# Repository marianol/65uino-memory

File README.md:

# 65uino Memory Hat

This is a hack Hat for the 65uino project to extend the memory to the maximum 4Kb minus the 256 bytes of Zero Page used by the RIOT memory and registers.

Is a hack Hat because it relocates the board ROM to the hat and uses pin headers to bring the ROM pins to the hat board. You will need to add some bodge wires to extend extra pins (A12 and R/WB) not available in the ROM socket.

This board has not been tested as of Rev. 0.2

## Memory Map
RIOT $0000-$00FF
RAM  $0100-$0FFF
ROM  $1000-$1FFF

## 65uino Project
The project author is Anders Nielsen and you can findit here https://github.com/AndersBNielsen/65uino/
You'll find more details at https://hackaday.io/project/190260-65uino

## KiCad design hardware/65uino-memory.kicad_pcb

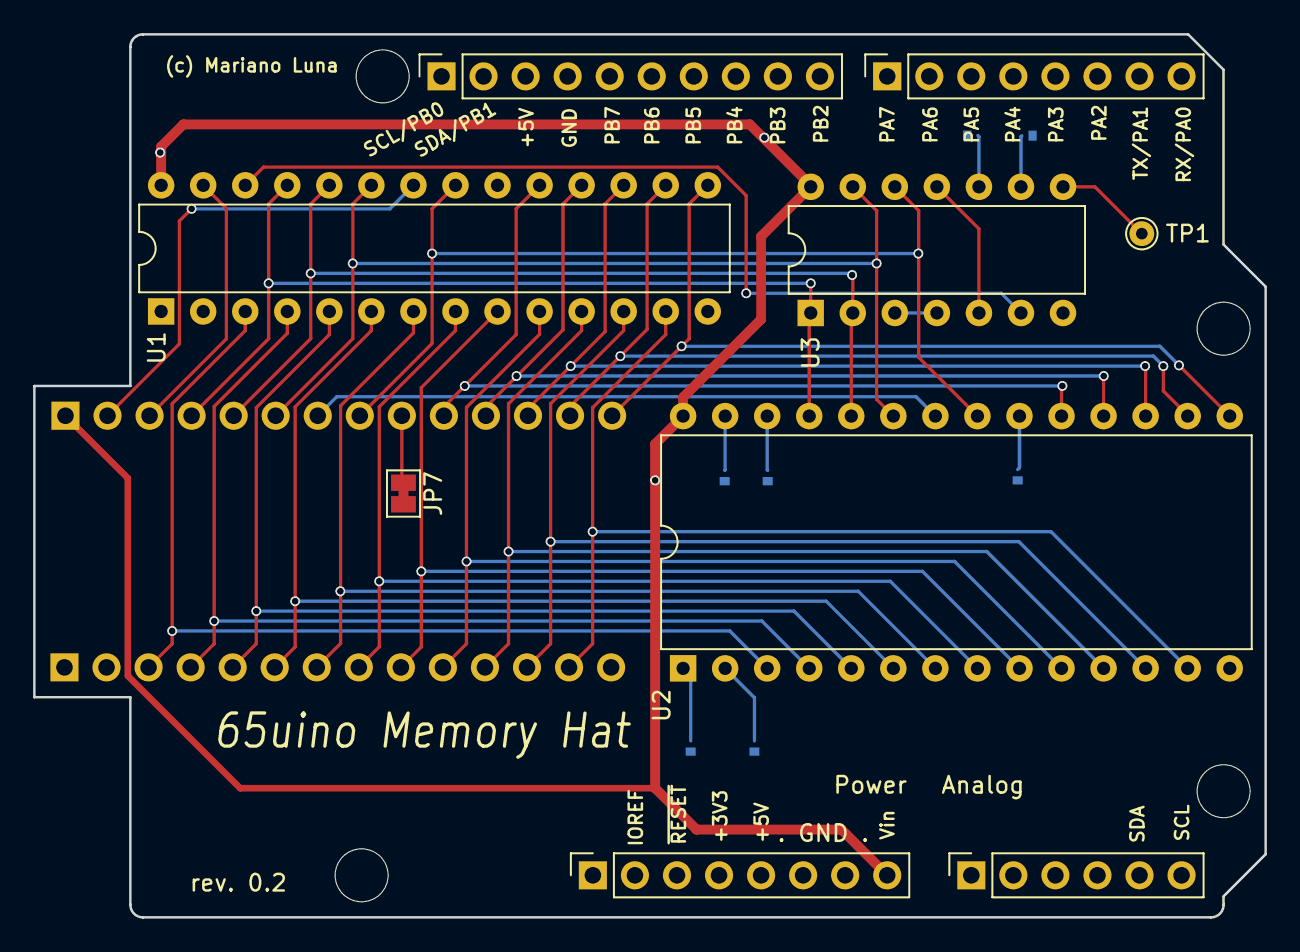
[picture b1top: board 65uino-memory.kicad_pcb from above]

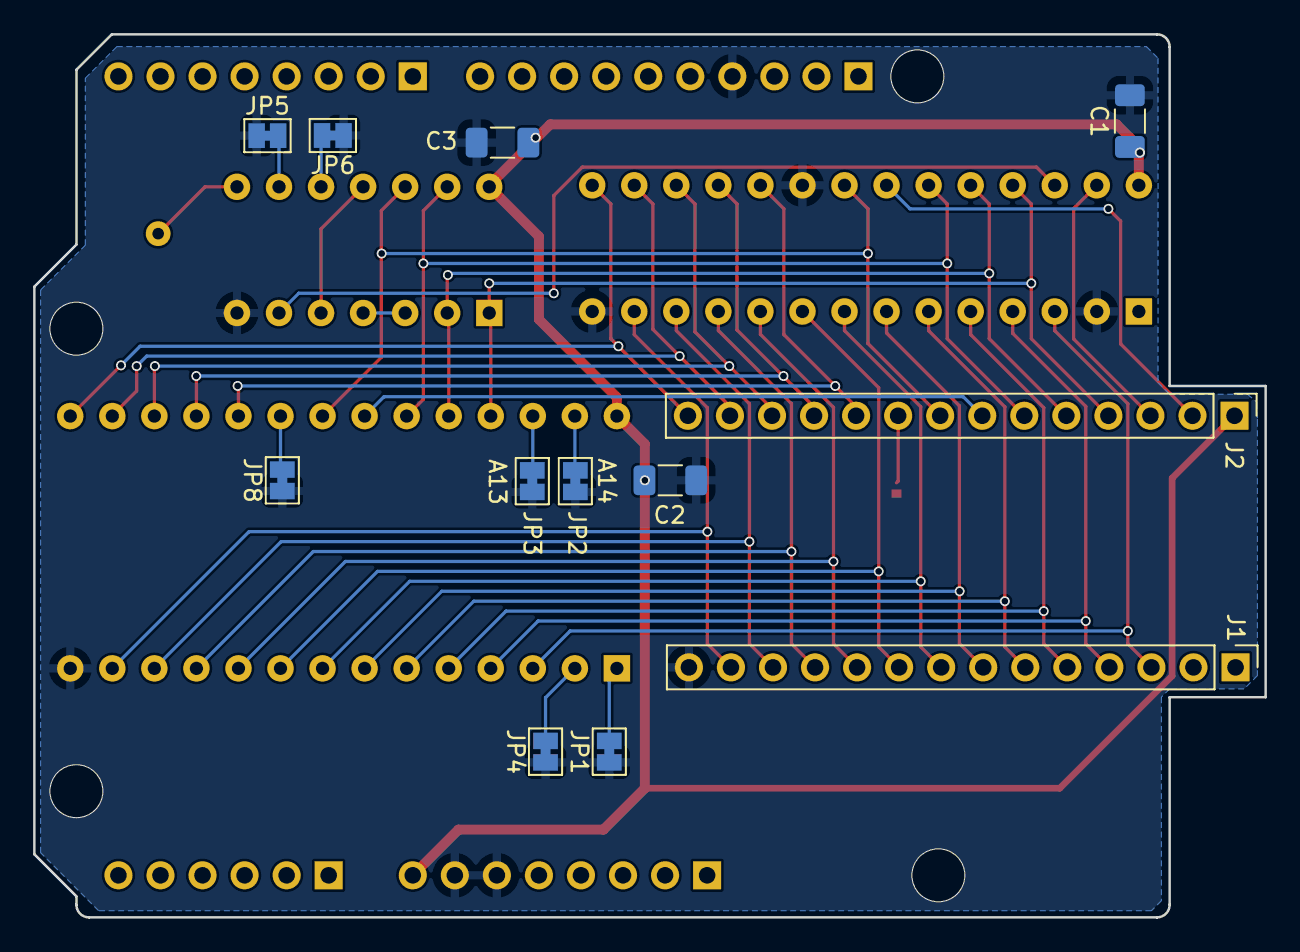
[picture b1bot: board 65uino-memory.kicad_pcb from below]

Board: 2 copper layers, 74.4 x 53.3 mm, 25 parts (12 on the bottom side), 37 nets.

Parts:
C1, C2, C3: C; C_1206_3216Metric_Pad1.33x1.80mm_HandSolder
J1, J2: Conn_01x14_Pin; PinHeader_1x14_P2.54mm_Vertical
J3: Digital/PWM; PinSocket_1x10_P2.54mm_Vertical
J4: Power; PinSocket_1x08_P2.54mm_Vertical
J5: Analog; PinSocket_1x06_P2.54mm_Vertical
J6: Digital/PWM; PinSocket_1x08_P2.54mm_Vertical
JP1: A15; SolderJumper-2_P1.3mm_Bridged_Pad1.0x1.5mm
JP2: A14; SolderJumper-2_P1.3mm_Bridged_Pad1.0x1.5mm
JP3: A13; SolderJumper-2_P1.3mm_Bridged_Pad1.0x1.5mm
JP4: A12; SolderJumper-2_P1.3mm_Bridged_Pad1.0x1.5mm
JP5, JP6: SolderJumper-2_P1.3mm_Bridged_Pad1.0x1.5mm
JP7, JP8: CE; SolderJumper-2_P1.3mm_Bridged_Pad1.0x1.5mm
MH1, MH2, MH3, MH4: MountingHole_3.2mm
TP1: TestPoint_THTPad_D1.5mm_Drill0.7mm
U1: AS7C164A-15PCN; DIP-28_W7.62mm
U2: 27C512; DIP-28_W15.24mm
U3: 74LS32; DIP-14_W7.62mm

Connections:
/GND/CE: J2.9, JP7.1 (A)
/~CE: JP8.2 (B), U2.20 (~CE)
A0: J1.10, U1.10 (A0), U2.10 (A0)
A1: J1.9, U1.9 (A1), U2.9 (A1)
A2: J1.8, U1.8 (A2), U2.8 (A2)
A3: J1.7, U1.7 (A3), U2.7 (A3)
A4: J1.6, U1.6 (A4), U2.6 (A4)
A5: J1.5, U1.5 (A5), U2.5 (A5)
A6: J1.4, U1.4 (A6), U2.4 (A6)
A7: J1.3, U1.3 (A7), U2.3 (A7)
A8: J2.4, U1.25 (A8), U2.25 (A8), U3.1
A9: J2.5, U1.24 (A9), U2.24 (A9), U3.2
A10: J2.8, U1.21 (A10), U2.21 (A10), U3.12
A11: J2.6, U1.23 (A11), U2.23 (A11), U3.13
A12: JP4.2 (B), U2.2 (A12)
A13: JP3.2 (B), U2.26 (A13)
A14: JP2.2 (B), U2.27 (A14)
A15: JP1.2 (B), U2.1 (A15)
D0: J1.11, U1.11 (Q0), U2.11 (D0)
D1: J1.12, U1.12 (Q1), U2.12 (D1)
D2: J1.13, U1.13 (Q2), U2.13 (D2)
D3: J2.14, U1.15 (Q3), U2.15 (D3)
D4: J2.13, U1.16 (Q4), U2.16 (D4)
D5: J2.12, U1.17 (Q5), U2.17 (D5)
D6: J2.11, U1.18 (Q6), U2.18 (D6)
D7: J2.10, U1.19 (Q7), U2.19 (D7)
GND: C1.2, C2.2, C3.2, J1.14, J3.4, J4.6, J4.7, JP1.1 (A), JP2.1 (A), JP3.1 (A), JP4.1 (A), JP5.1 (A), JP6.1 (A), JP8.1 (A), U1.2 (A12), U1.14 (GND), U1.20 (~CS), U2.14 (GND), U3.7 (GND)
JP2 ~WE: J2.3, U1.27 (~WE)
JP8 A12: J2.2, U1.22 (~OE)
unnamed: JP5.2 (B), U3.9
unnamed: JP6.2 (B), U3.10
unnamed: TP1.1, U3.8
unnamed: U3.3, U3.4
unnamed: U3.5, U3.11
RAM_CS2: U1.26 (CS2), U3.6
VCC: C1.1, C2.1, C3.1, J2.1, J4.8, U1.28 (VCC), U2.28 (VCC), U3.14 (VCC)
~A12: J2.7, U2.22 (~OE)

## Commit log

2024-01-18 First revision untested
